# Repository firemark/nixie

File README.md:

# nixie

* `make`
* `make fuse`
* `make flash`

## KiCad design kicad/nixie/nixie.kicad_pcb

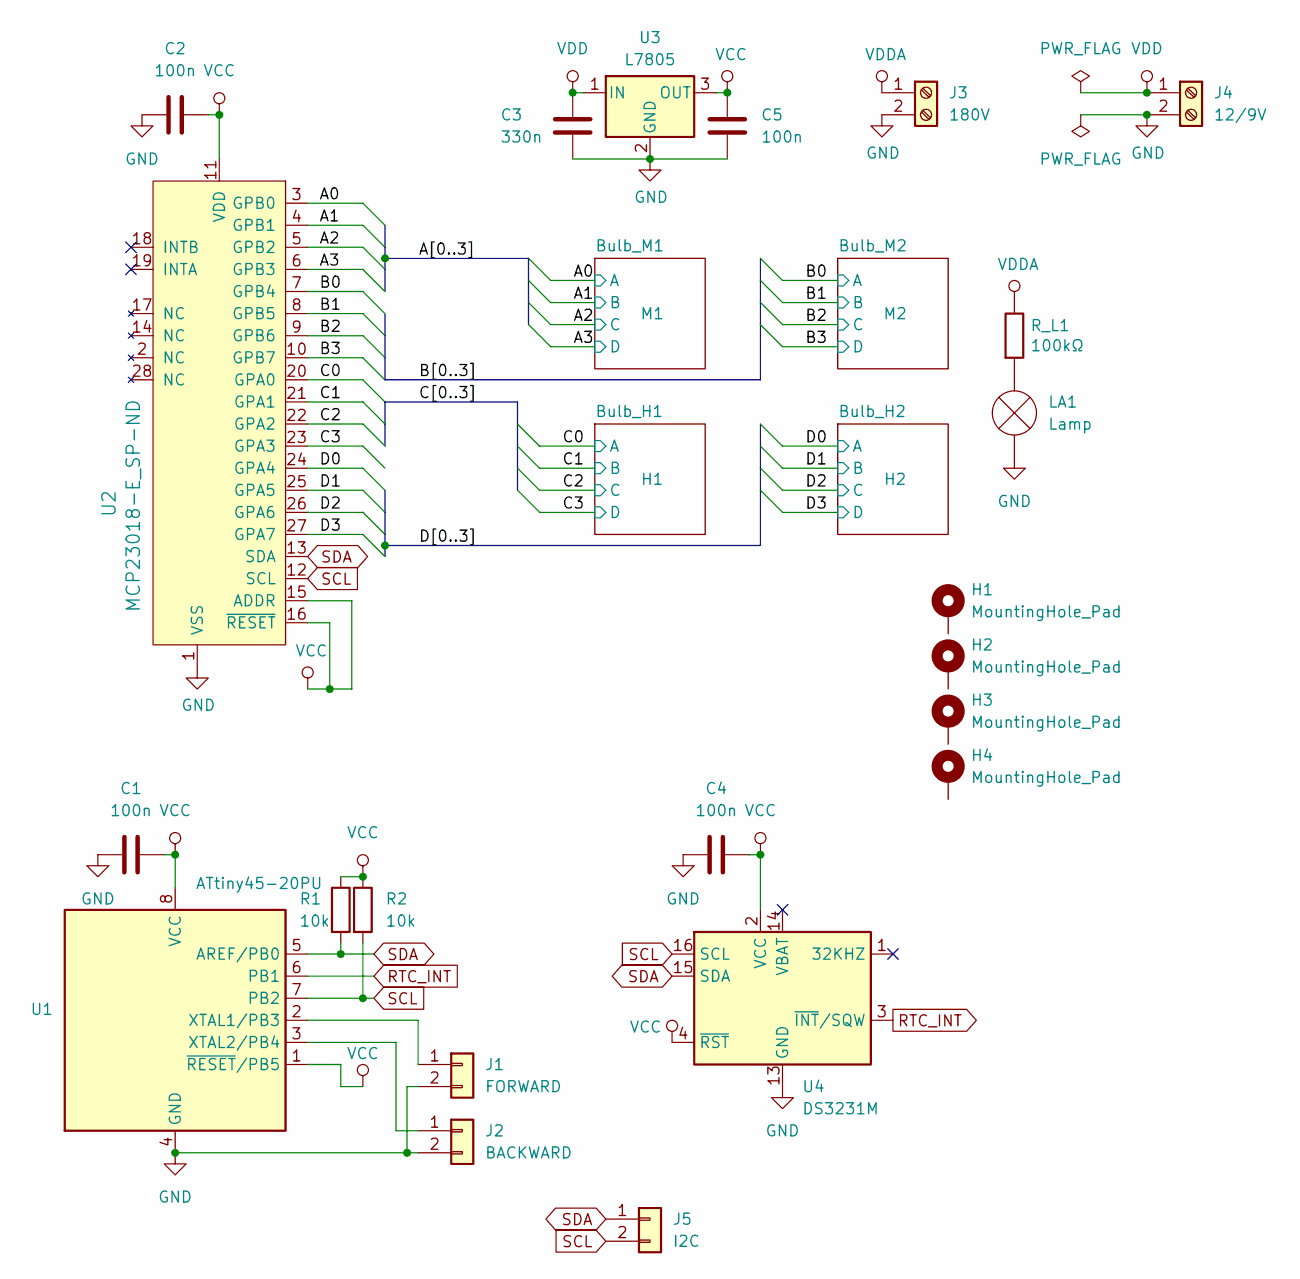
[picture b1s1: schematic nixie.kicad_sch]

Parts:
C1, C2, C4: 100n; C_1206_3216Metric
C3: 330n; C_Disc_D3.0mm_W1.6mm_P2.50mm
C5: 100n; C_Disc_D3.0mm_W1.6mm_P2.50mm
H1, H2, H3, H4: MountingHole_Pad; MountingHole_3.2mm_M3_Pad
J1: FORWARD; JST_EH_B2B-EH-A_1x02_P2.50mm_Vertical
J2: BACKWARD; JST_EH_B2B-EH-A_1x02_P2.50mm_Vertical
J3: 180V; TerminalBlock_Altech_AK300-2_P5.00mm
J4: 12/9V; TerminalBlock_Altech_AK300-2_P5.00mm
J5: I2C; JST_EH_B2B-EH-A_1x02_P2.50mm_Vertical
LA1: Lamp; LED_D1.8mm_W3.3mm_H2.4mm
R1, R2: 10k; R_1206_3216Metric
R_L1: 100kΩ; R_Axial_DIN0204_L3.6mm_D1.6mm_P7.62mm_Horizontal
U1: ATtiny45-20PU; DIP-8_W7.62mm
U2: MCP23018-E_SP-ND; DIP-28_W7.62mm
U3: L7805; TO-220-3_Horizontal_TabDown
U4: DS3231M; SOIC-16W_7.5x10.3mm_P1.27mm

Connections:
/A0: U2.3 (GPB0); also elsewhere on the board
/A1: U2.4 (GPB1); also elsewhere on the board
/A2: U2.5 (GPB2); also elsewhere on the board
/A3: U2.6 (GPB3); also elsewhere on the board
/B0: U2.7 (GPB4); also elsewhere on the board
/B1: U2.8 (GPB5); also elsewhere on the board
/B2: U2.9 (GPB6); also elsewhere on the board
/B3: U2.10 (GPB7); also elsewhere on the board
/C0: U2.20 (GPA0); also elsewhere on the board
/C1: U2.21 (GPA1); also elsewhere on the board
/C2: U2.22 (GPA2); also elsewhere on the board
/C3: U2.23 (GPA3); also elsewhere on the board
/D0: U2.24 (GPA4); also elsewhere on the board
/D1: U2.25 (GPA5); also elsewhere on the board
/D2: U2.26 (GPA6); also elsewhere on the board
/D3: U2.27 (GPA7); also elsewhere on the board
GND: C1.1, C2.1, C3.2, C4.1, C5.2, J1.2, J2.2, J3.2, J4.2, LA1.1 (-), U1.4 (GND), U2.1 (VSS), U3.2 (GND), U4.5 (GND), U4.6 (GND), U4.7 (GND), U4.8 (GND), U4.9 (GND), U4.10 (GND), U4.11 (GND), U4.12 (GND), U4.13 (GND); also elsewhere on the board
unnamed: J1.1, U1.2 (XTAL1/PB3)
unnamed: J2.1, U1.3 (XTAL2/PB4)
unnamed: LA1.2 (+), R_L1.2
RTC_INT: U1.6 (PB1), U4.3 (~INT/SQW)
SCL: J5.2, R2.2, U1.7 (PB2), U2.12 (SCL), U4.16 (SCL)
SDA: J5.1, R1.2, U1.5 (AREF/PB0), U2.13 (SDA), U4.15 (SDA)
VCC: C1.2, C2.2, C4.2, C5.1, R1.1, R2.1, U1.1 (~RESET/PB5), U1.8 (VCC), U2.11 (VDD), U2.15 (ADDR), U2.16 (~RESET), U3.3 (OUT), U4.2 (VCC), U4.4 (~RST); also elsewhere on the board
VDD: C3.1, J4.1, U3.1 (IN)
VDDA: J3.1, R_L1.1; also elsewhere on the board

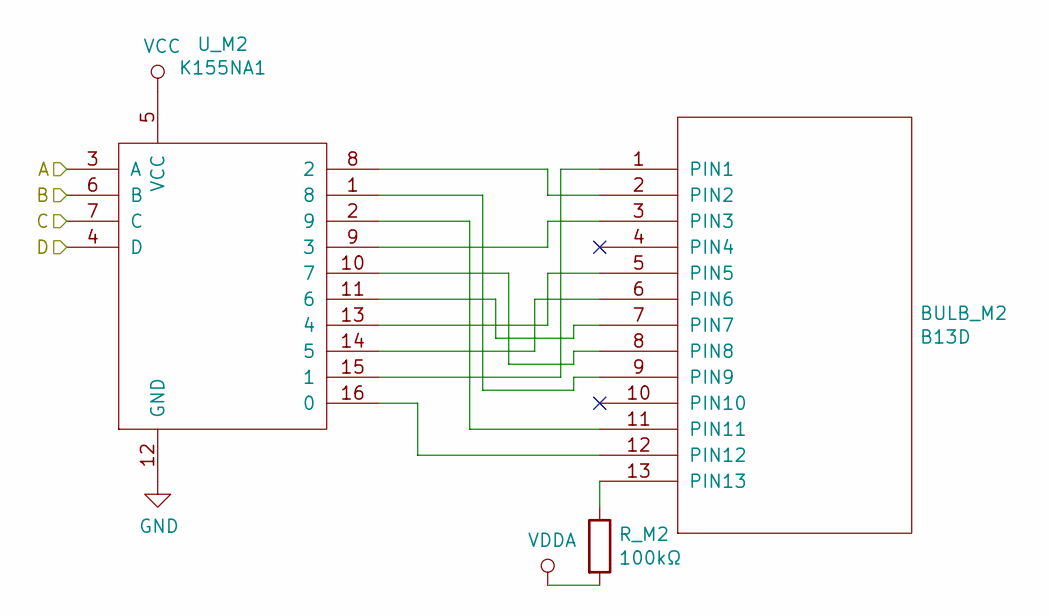
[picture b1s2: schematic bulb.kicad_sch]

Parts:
BULB_M2: B13D; b13d
R_M2: 100kΩ; R_Axial_DIN0204_L3.6mm_D1.6mm_P7.62mm_Horizontal
U_M2: K155NA1; DIP-16_W7.62mm

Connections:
/B0: U_M2.3 (A); also elsewhere on the board
/B1: U_M2.6 (B); also elsewhere on the board
/B2: U_M2.7 (C); also elsewhere on the board
/B3: U_M2.4 (D); also elsewhere on the board
GND: U_M2.12 (GND); also elsewhere on the board
unnamed: BULB_M2.1 (PIN1), U_M2.15 (1)
unnamed: BULB_M2.2 (PIN2), U_M2.8 (2)
unnamed: BULB_M2.3 (PIN3), U_M2.9 (3)
unnamed: BULB_M2.5 (PIN5), U_M2.13 (4)
unnamed: BULB_M2.6 (PIN6), U_M2.14 (5)
unnamed: BULB_M2.7 (PIN7), U_M2.11 (6)
unnamed: BULB_M2.8 (PIN8), U_M2.10 (7)
unnamed: BULB_M2.9 (PIN9), U_M2.1 (8)
unnamed: BULB_M2.11 (PIN11), U_M2.2 (9)
unnamed: BULB_M2.12 (PIN12), U_M2.16 (0)
unnamed: BULB_M2.13 (PIN13), R_M2.1
VCC: U_M2.5 (VCC); also elsewhere on the board
VDDA: R_M2.2; also elsewhere on the board

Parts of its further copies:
BULB_H1, BULB_H2: B13D; b13d
BULB_M1: B13D; b13d
R_H1, R_H2: 100kΩ; R_Axial_DIN0204_L3.6mm_D1.6mm_P7.62mm_Horizontal
R_M1: 100kΩ; R_Axial_DIN0204_L3.6mm_D1.6mm_P7.62mm_Horizontal
U_H1, U_H2: K155NA1; DIP-16_W7.62mm
U_M1: K155NA1; DIP-16_W7.62mm

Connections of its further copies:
/A0: U_M1.3 (A); also elsewhere on the board
/A1: U_M1.6 (B); also elsewhere on the board
/A2: U_M1.7 (C); also elsewhere on the board
/A3: U_M1.4 (D); also elsewhere on the board
/C0: U_H1.3 (A); also elsewhere on the board
/C1: U_H1.6 (B); also elsewhere on the board
/C2: U_H1.7 (C); also elsewhere on the board
/C3: U_H1.4 (D); also elsewhere on the board
/D0: U_H2.3 (A); also elsewhere on the board
/D1: U_H2.6 (B); also elsewhere on the board
/D2: U_H2.7 (C); also elsewhere on the board
/D3: U_H2.4 (D); also elsewhere on the board
GND: U_H1.12 (GND), U_H2.12 (GND), U_M1.12 (GND); also elsewhere on the board
unnamed: BULB_H1.1 (PIN1), U_H1.15 (1)
unnamed: BULB_H1.2 (PIN2), U_H1.8 (2)
unnamed: BULB_H1.3 (PIN3), U_H1.9 (3)
unnamed: BULB_H1.5 (PIN5), U_H1.13 (4)
unnamed: BULB_H1.6 (PIN6), U_H1.14 (5)
unnamed: BULB_H1.7 (PIN7), U_H1.11 (6)
unnamed: BULB_H1.8 (PIN8), U_H1.10 (7)
unnamed: BULB_H1.9 (PIN9), U_H1.1 (8)
unnamed: BULB_H1.11 (PIN11), U_H1.2 (9)
unnamed: BULB_H1.12 (PIN12), U_H1.16 (0)
unnamed: BULB_H1.13 (PIN13), R_H1.1
unnamed: BULB_H2.1 (PIN1), U_H2.15 (1)
unnamed: BULB_H2.2 (PIN2), U_H2.8 (2)
unnamed: BULB_H2.3 (PIN3), U_H2.9 (3)
unnamed: BULB_H2.5 (PIN5), U_H2.13 (4)
unnamed: BULB_H2.6 (PIN6), U_H2.14 (5)
unnamed: BULB_H2.7 (PIN7), U_H2.11 (6)
unnamed: BULB_H2.8 (PIN8), U_H2.10 (7)
unnamed: BULB_H2.9 (PIN9), U_H2.1 (8)
unnamed: BULB_H2.11 (PIN11), U_H2.2 (9)
unnamed: BULB_H2.12 (PIN12), U_H2.16 (0)
unnamed: BULB_H2.13 (PIN13), R_H2.1
unnamed: BULB_M1.1 (PIN1), U_M1.15 (1)
unnamed: BULB_M1.2 (PIN2), U_M1.8 (2)
unnamed: BULB_M1.3 (PIN3), U_M1.9 (3)
unnamed: BULB_M1.5 (PIN5), U_M1.13 (4)
unnamed: BULB_M1.6 (PIN6), U_M1.14 (5)
unnamed: BULB_M1.7 (PIN7), U_M1.11 (6)
unnamed: BULB_M1.8 (PIN8), U_M1.10 (7)
unnamed: BULB_M1.9 (PIN9), U_M1.1 (8)
unnamed: BULB_M1.11 (PIN11), U_M1.2 (9)
unnamed: BULB_M1.12 (PIN12), U_M1.16 (0)
unnamed: BULB_M1.13 (PIN13), R_M1.1
VCC: U_H1.5 (VCC), U_H2.5 (VCC), U_M1.5 (VCC); also elsewhere on the board
VDDA: R_H1.2, R_H2.2, R_M1.2; also elsewhere on the board

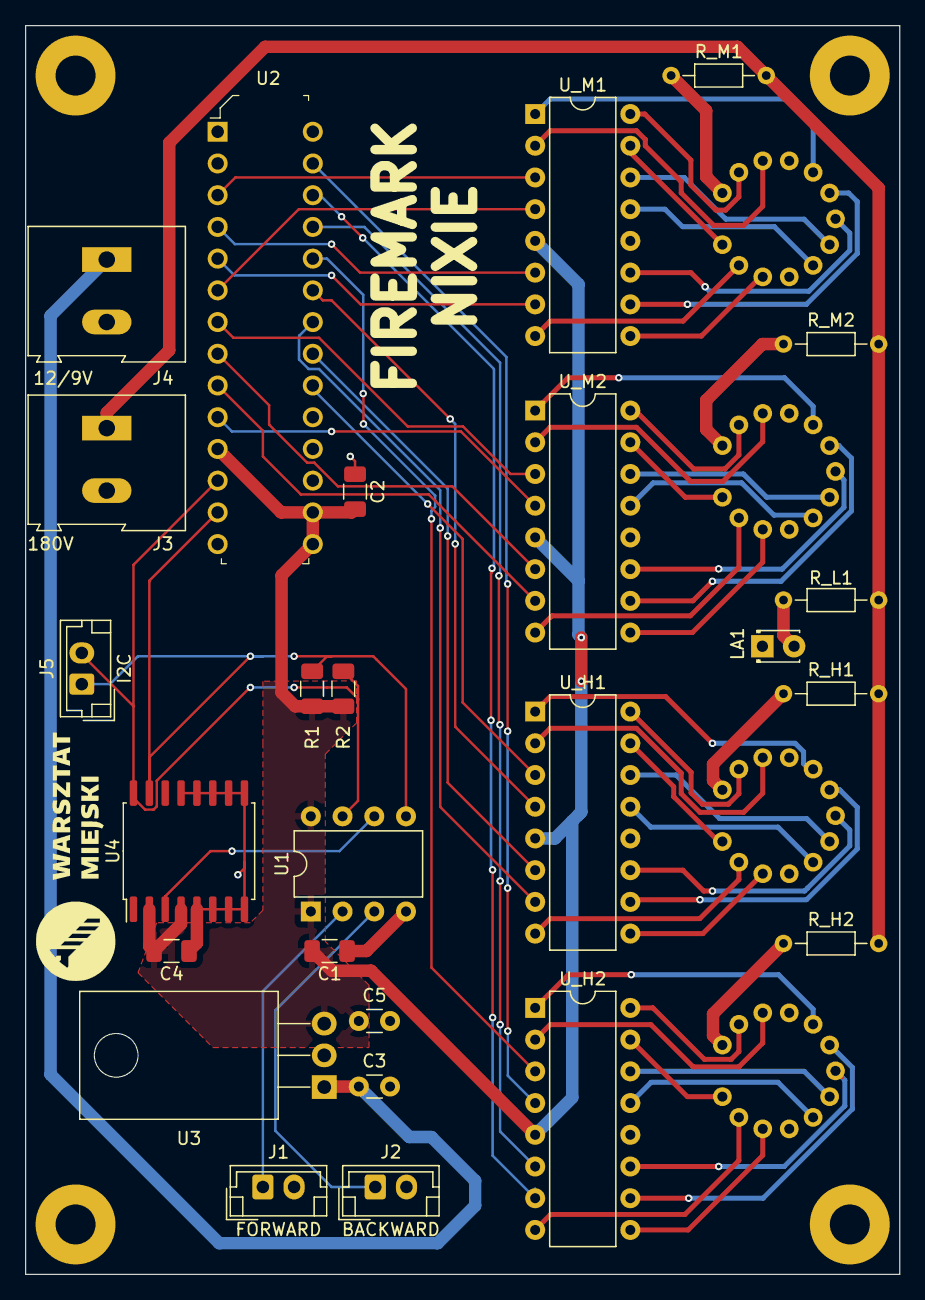
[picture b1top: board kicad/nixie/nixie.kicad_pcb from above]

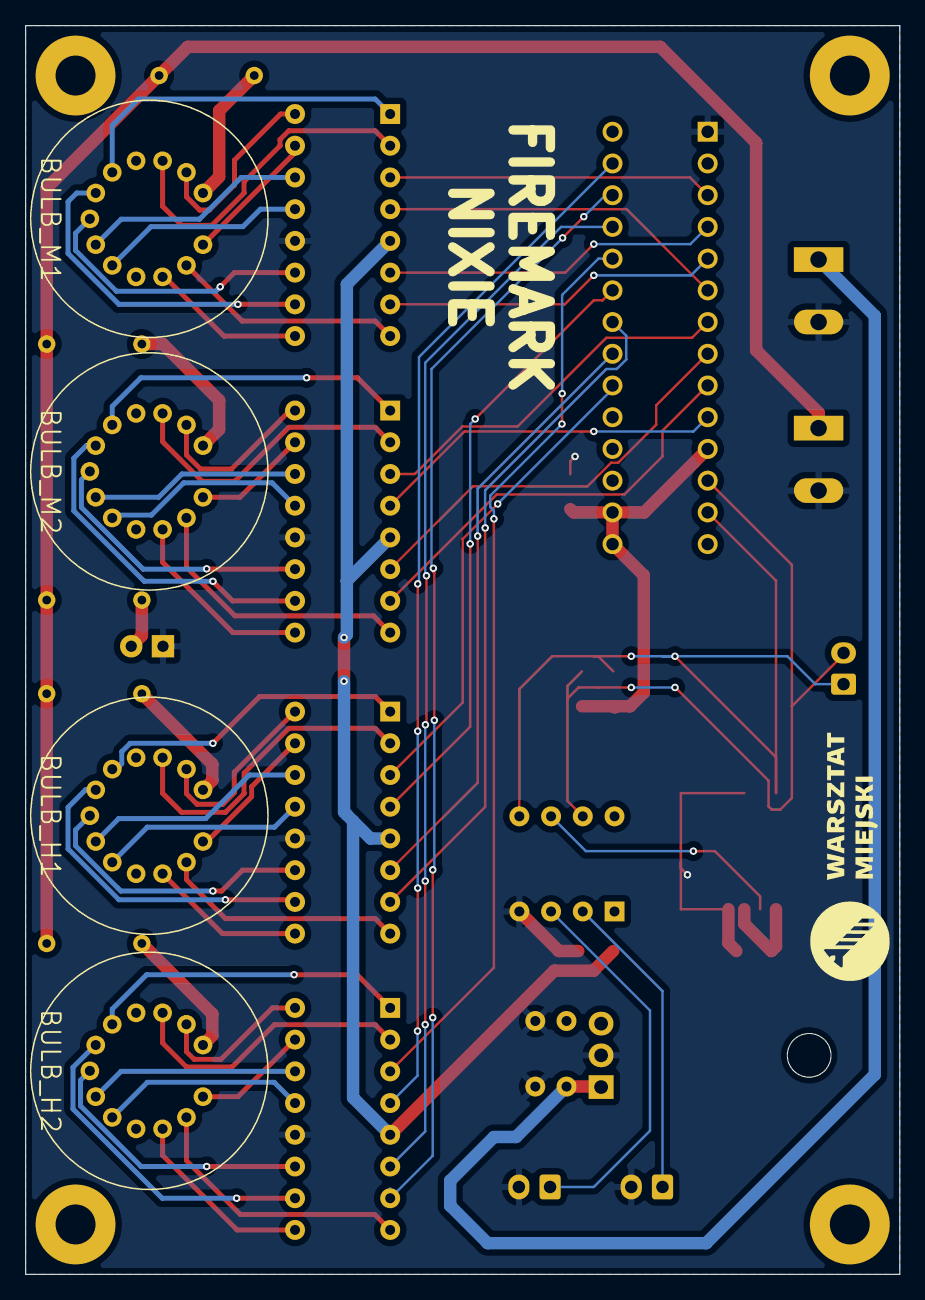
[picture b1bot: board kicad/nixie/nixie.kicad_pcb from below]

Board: 2 copper layers, 70.0 x 100.0 mm, 34 parts (4 on the bottom side), 70 nets.

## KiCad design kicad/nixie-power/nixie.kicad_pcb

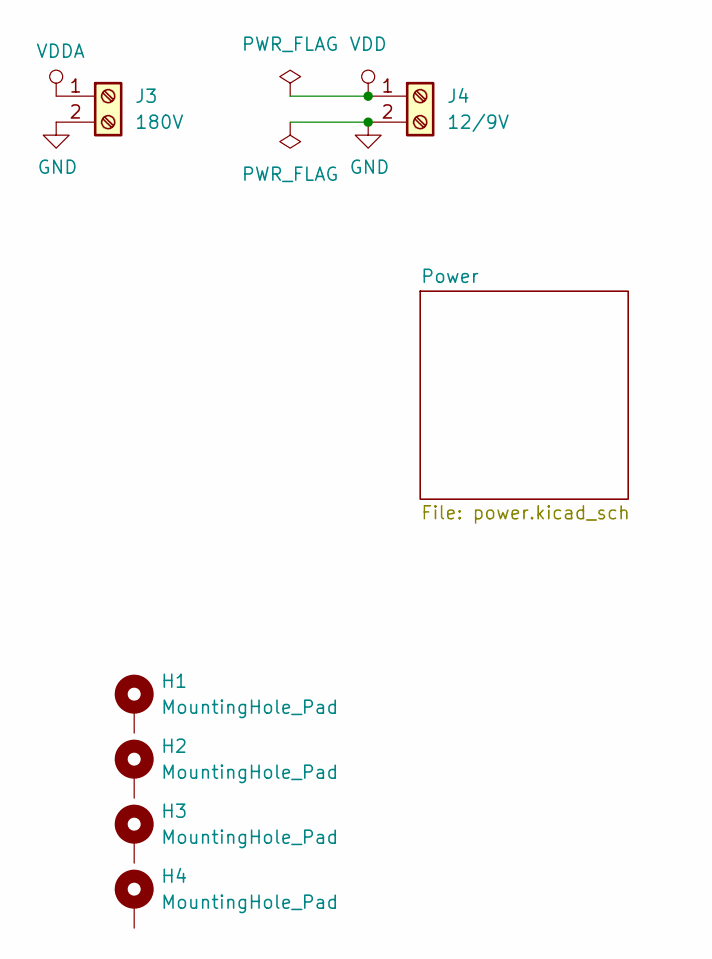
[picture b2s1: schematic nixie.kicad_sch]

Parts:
H1, H2, H3, H4: MountingHole_Pad; MountingHole_3.2mm_M3_Pad
J3: 180V; TerminalBlock_Altech_AK300-2_P5.00mm
J4: 12/9V; TerminalBlock_Altech_AK300-2_P5.00mm

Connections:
GND: J3.2, J4.2; also elsewhere on the board
VDD: J4.1; also elsewhere on the board
VDDA: J3.1; also elsewhere on the board

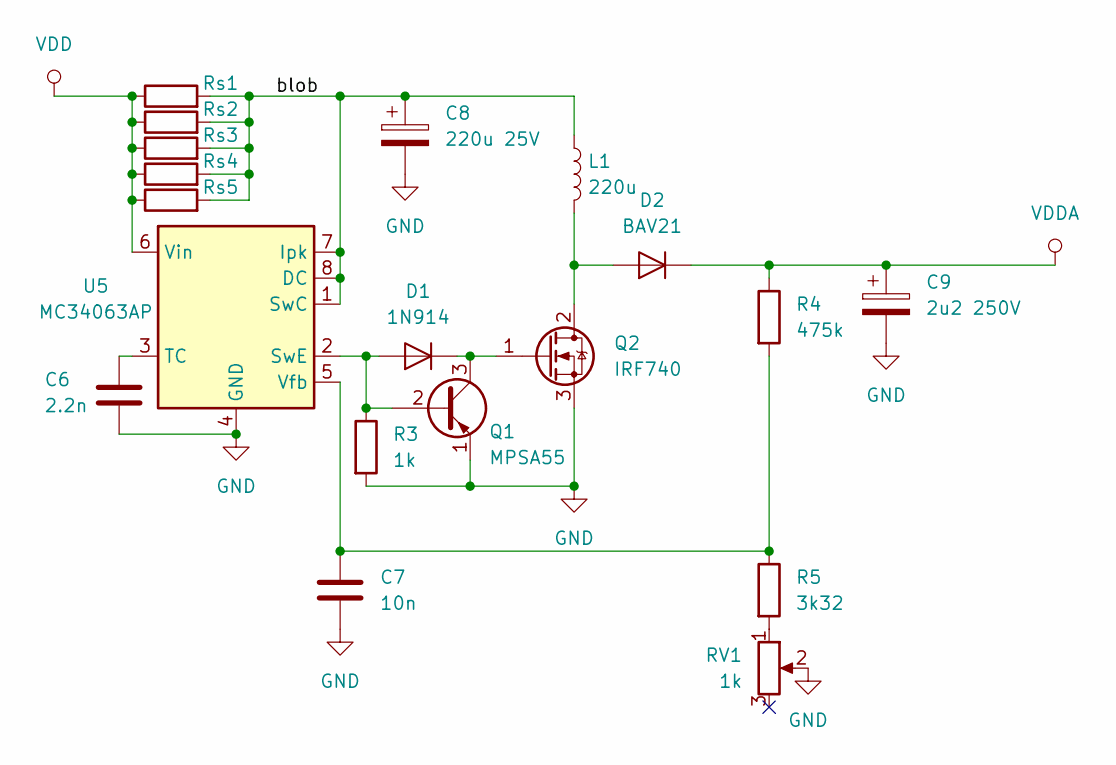
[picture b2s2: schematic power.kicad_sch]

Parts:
C6: 2.2n; C_Disc_D3.0mm_W1.6mm_P2.50mm
C7: 10n; C_Disc_D3.0mm_W1.6mm_P2.50mm
C8: 220u 25V; CP_Radial_Tantal_D8.0mm_P5.00mm
C9: 2u2 250V; CP_Radial_D22.0mm_P10.00mm_SnapIn
D1: 1N914; D_DO-35_SOD27_P7.62mm_Horizontal
D2: BAV21; D_DO-35_SOD27_P7.62mm_Horizontal
L1: 220u; L_Radial_D9.5mm_P5.00mm_Fastron_07HVP
Q1: MPSA55; TO-92_Inline
Q2: IRF740; TO-220-3_Vertical
R3: 1k; R_Axial_DIN0207_L6.3mm_D2.5mm_P10.16mm_Horizontal
R4: 475k; R_Axial_DIN0207_L6.3mm_D2.5mm_P10.16mm_Horizontal
R5: 3k32; R_Axial_DIN0207_L6.3mm_D2.5mm_P10.16mm_Horizontal
RV1: 1k; Potentiometer_Bourns_3296P_Horizontal
Rs1, Rs2, Rs3, Rs4, Rs5: 1; R_Axial_DIN0207_L6.3mm_D2.5mm_P10.16mm_Horizontal
U5: MC34063AP; DIP-8_W7.62mm

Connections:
/Power/blob: C8.1, L1.1, Rs1.2, Rs2.2, Rs3.2, Rs4.2, Rs5.2, U5.1 (SwC), U5.7 (Ipk), U5.8 (DC)
GND: C6.2, C7.2, C8.2, C9.2, Q1.1 (E), Q2.3 (S), R3.2, RV1.2, U5.4 (GND); also elsewhere on the board
unnamed: D1.2 (A), Q1.2 (B), R3.1, U5.2 (SwE)
unnamed: D1.1 (K), Q1.3 (C), Q2.1 (G)
unnamed: D2.2 (A), L1.2, Q2.2 (D)
unnamed: R5.2, RV1.1
unnamed: C6.1, U5.3 (TC)
unnamed: C7.1, R4.2, R5.1, U5.5 (Vfb)
VDD: Rs1.1, Rs2.1, Rs3.1, Rs4.1, Rs5.1, U5.6 (Vin); also elsewhere on the board
VDDA: C9.1, D2.1 (K), R4.1; also elsewhere on the board

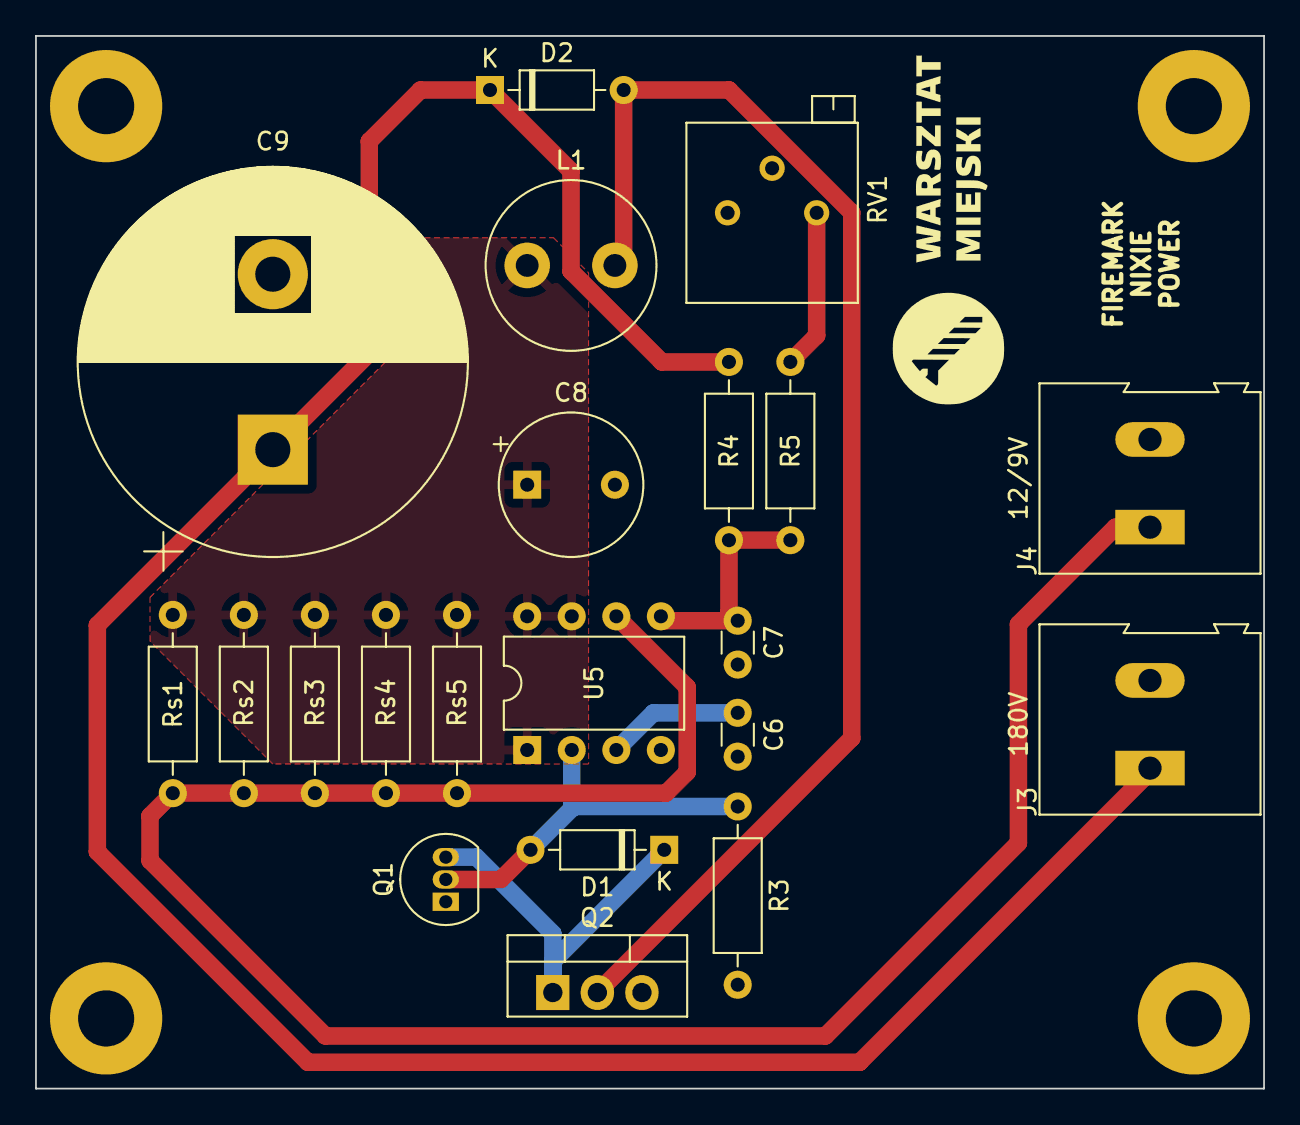
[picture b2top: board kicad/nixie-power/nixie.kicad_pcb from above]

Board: 2 copper layers, 70.0 x 60.0 mm, 25 parts (0 on the bottom side), 10 nets.

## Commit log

2026-06-04 Add final project
2026-06-05 Add multiplexering to reduce current
